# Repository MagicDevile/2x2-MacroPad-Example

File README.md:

# 2x2-MacroPad-Example
 Intro KiCad project

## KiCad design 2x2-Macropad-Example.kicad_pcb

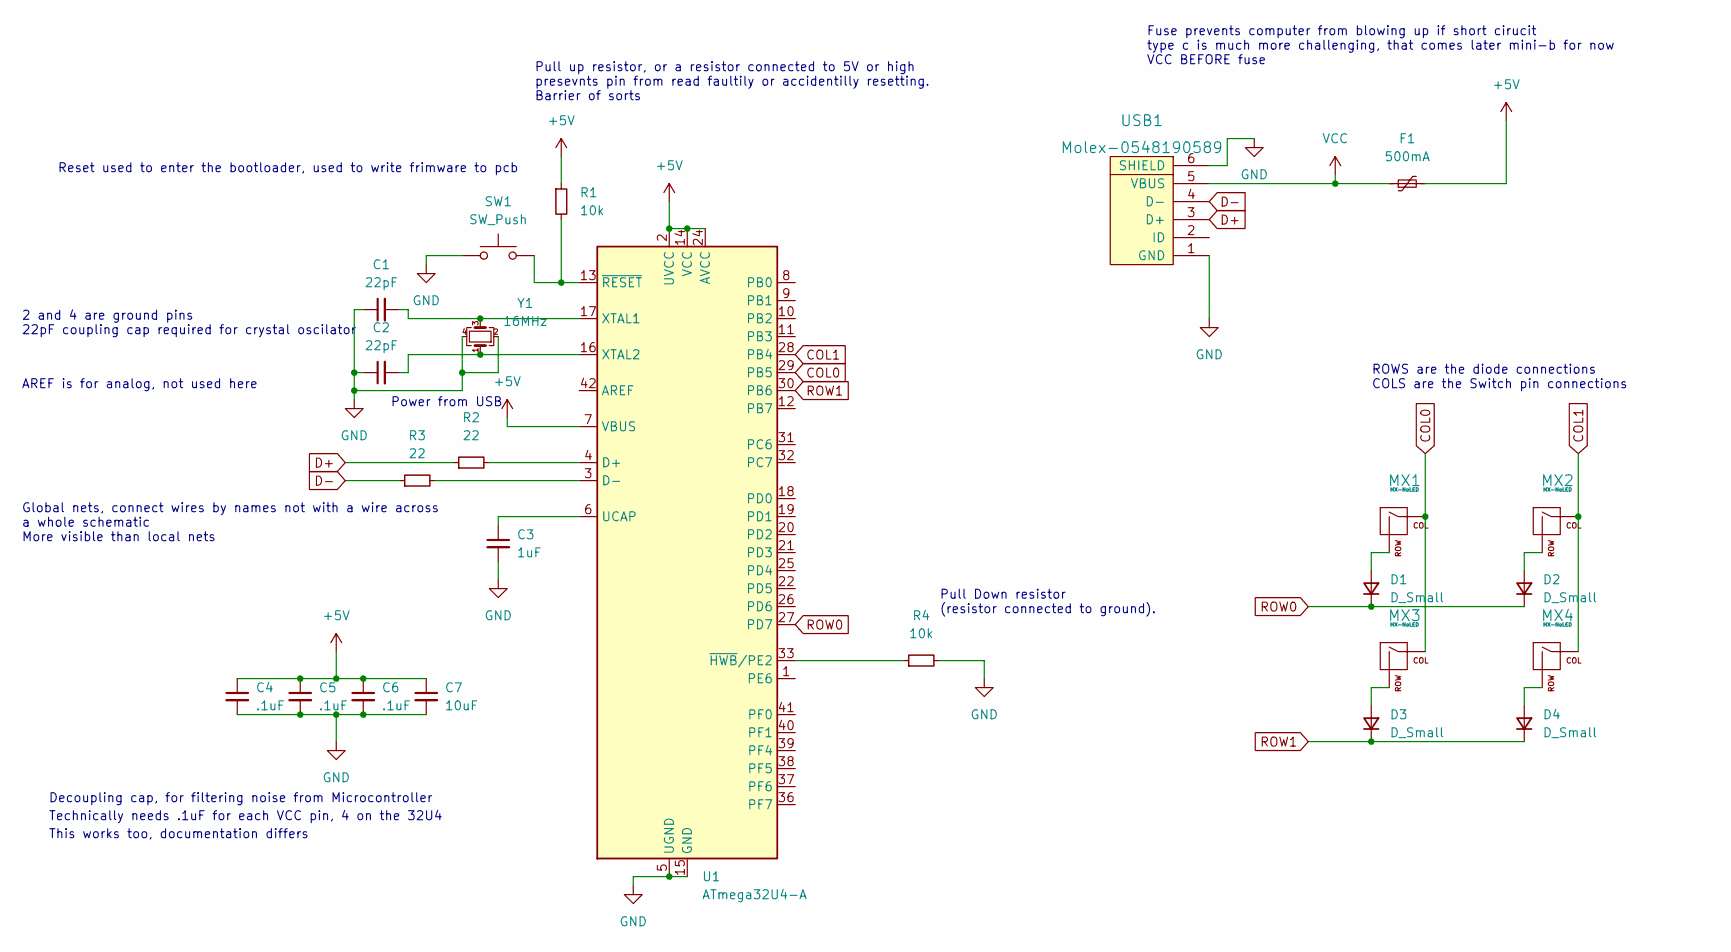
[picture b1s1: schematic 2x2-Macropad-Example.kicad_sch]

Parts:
C1, C2: 22pF; C_0805_2012Metric
C3: 1uF; C_0805_2012Metric
C4, C5, C6: .1uF; C_0805_2012Metric
C7: 10uF; C_0805_2012Metric
D1, D2, D3, D4: D_Small; D_SOD-123
F1: 500mA; Fuse_1206_3216Metric
MX1, MX2, MX3, MX4: MX-NoLED; MX-1U
R1, R4: 10k; R_0805_2012Metric
R2, R3: 22; R_0805_2012Metric
SW1: SW_Push; SKQG-1155865
U1: ATmega32U4-A; TQFP-44_10x10mm_P0.8mm
USB1: Molex-0548190589
Y1: 16MHz; Crystal_SMD_3225-4Pin_3.2x2.5mm

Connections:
+5V: C4.1, C5.1, C6.1, C7.1, F1.2, R1.1, U1.2 (UVCC), U1.7 (VBUS), U1.14 (VCC), U1.24 (AVCC), U1.34 (VCC), U1.44 (AVCC)
COL0: MX1.1 (COL), MX3.1 (COL), U1.29 (PB5)
COL1: MX2.1 (COL), MX4.1 (COL), U1.28 (PB4)
D+: R2.1, USB1.3 (D+)
D-: R3.1, USB1.4 (D-)
GND: C1.1, C2.1, C3.2, C4.2, C5.2, C6.2, C7.2, R4.2, SW1.1, U1.5 (UGND), U1.15 (GND), U1.23 (GND), U1.35 (GND), U1.43 (GND), USB1.1 (GND), USB1.6 (SHIELD), Y1.2, Y1.4
unnamed: C1.2, U1.17 (XTAL1), Y1.3
unnamed: C2.2, U1.16 (XTAL2), Y1.1
unnamed: C3.1, U1.6 (UCAP)
unnamed: D1.2 (A), MX1.2 (ROW)
unnamed: D2.2 (A), MX2.2 (ROW)
unnamed: D3.2 (A), MX3.2 (ROW)
unnamed: D4.2 (A), MX4.2 (ROW)
unnamed: R1.2, SW1.2, U1.13 (~RESET)
unnamed: R2.2, U1.4 (D+)
unnamed: R3.2, U1.3 (D-)
unnamed: R4.1, U1.33 (~HWB/PE2)
ROW0: D1.1 (K), D2.1 (K), U1.27 (PD7)
ROW1: D3.1 (K), D4.1 (K), U1.30 (PB6)
VCC: F1.1, USB1.5 (VBUS)

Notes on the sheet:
Decoupling cap, for filtering noise from Microcontroller
Reset used to enter the bootloader, used to write frimware to pcb
Global nets, connect wires by names not with a wire across a whole schematic More visible than local nets
This works too, documentation differs
AREF is for analog, not used here
Fuse prevents computer from blowing up if short cirucit type c is much more challenging, that comes later mini-b for now VCC BEFORE fuse
2 and 4 are ground pins 22pF coupling cap required for crystal oscilator
Technically needs .1uF for each VCC pin, 4 on the 32U4
Power from USB
Pull up resistor, or a resistor connected to 5V or high presevnts pin from read faultily or accidentilly resetting. Barrier of sorts
Pull Down resistor (resistor connected to ground).
ROWS are the diode connections COLS are the Switch pin connections

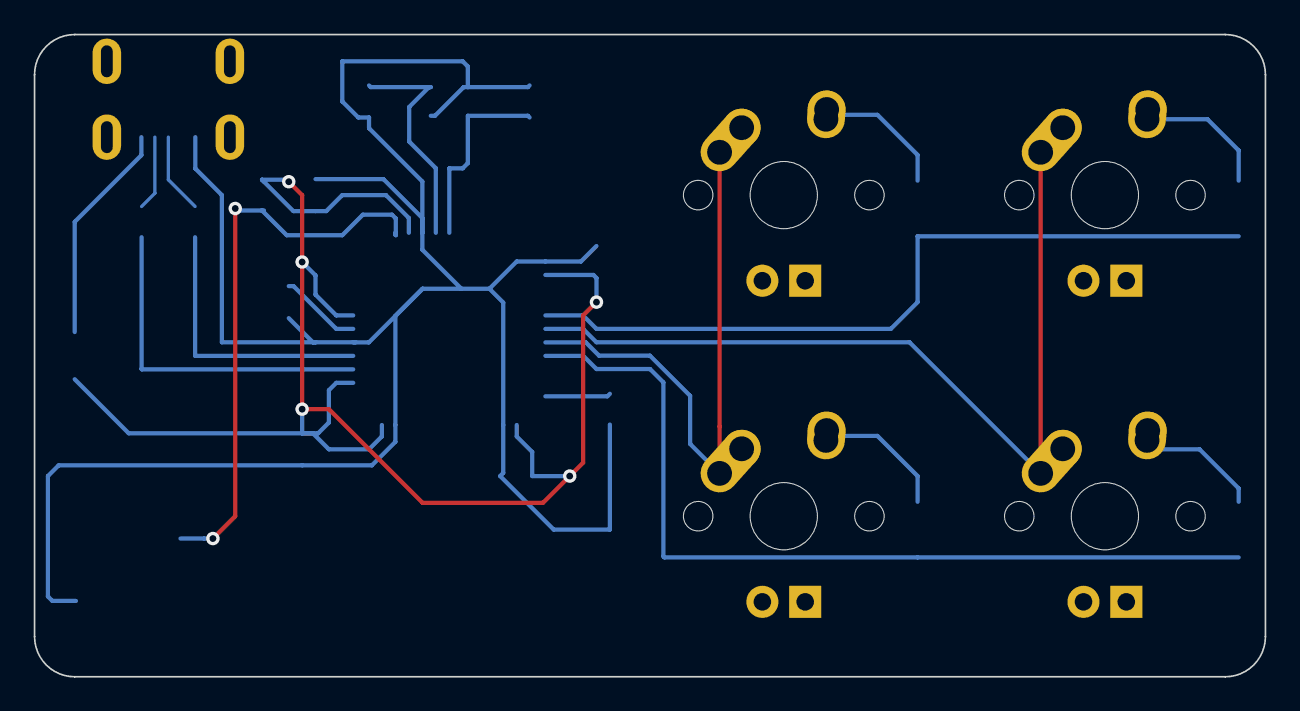
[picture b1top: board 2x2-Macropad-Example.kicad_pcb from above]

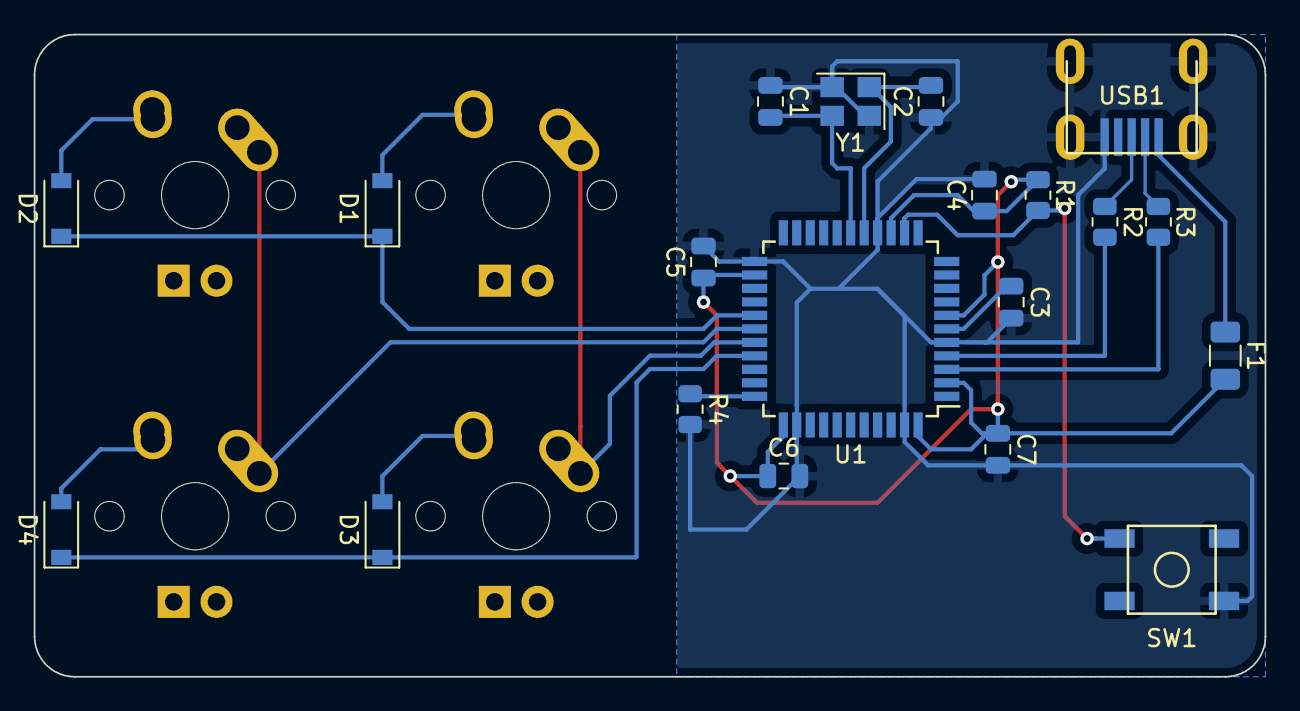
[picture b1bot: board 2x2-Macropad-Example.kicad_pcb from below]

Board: 2 copper layers, 73.0 x 38.1 mm, 24 parts (20 on the bottom side), 20 nets.

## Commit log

2022-01-23 Project Files
    KiCad Project Files
2022-01-23 Added submodules for keyboard components
2022-01-23 Added Project specific libraries
    added project library files .lib for schematic and .pretty folders for pcb footprints
2022-01-24 Schematic Finished
2022-01-24 pcb layout done
2022-01-24 beginning trace layout
2022-01-25 mostly finished routing the traces
2022-01-27 finished routing and laying fills, DRC issue with usb and mx footprints
2022-01-28 finalized design
